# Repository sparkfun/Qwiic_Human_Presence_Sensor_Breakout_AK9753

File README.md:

SparkFun Qwiic Human Presence Sensor (AK9753)
========================================

[*SparkFun Qwiic Human Presence Sensor (SEN-14349)*](https://www.sparkfun.com/products/14349)

The AK9753 Human Presence Sensor is a 4 channel NDIR sensor meant to detect human movement.

Repository Contents
-------------------

* **/Hardware** - Eagle design files (.brd, .sch)
* **/Libraries** - Libraries for use with the SparkFun Human Presence Sensor Breakout - AK9753 (Qwiic).
* **/Production** - Production panel files (.brd)

Documentation
--------------
* **[Library](https://github.com/sparkfun/SparkFun_AK975x_Arduino_Library)** - Arduino library for the AK9753.
* **[Hookup Guide](https://learn.sparkfun.com/tutorials/qwiic-human-presence-sensor-ak9753-hookup-guide)** - Basic hookup guide for the Qwiic Human Presence Sensor.

Product Versions
----------------
* [SEN-14349](https://www.sparkfun.com/products/14349)- The AK9753 Human Presence Sensor is a 4 channel NDIR sensor meant to detect human movement.

License Information
-------------------

This product is _**open source**_! 

Please review the LICENSE.md file for license information. 

If you have any questions or concerns on licensing, please contact techsupport@sparkfun.com.

Distributed as-is; no warranty is given.

- Your friends at SparkFun.

_<COLLABORATION CREDIT>_

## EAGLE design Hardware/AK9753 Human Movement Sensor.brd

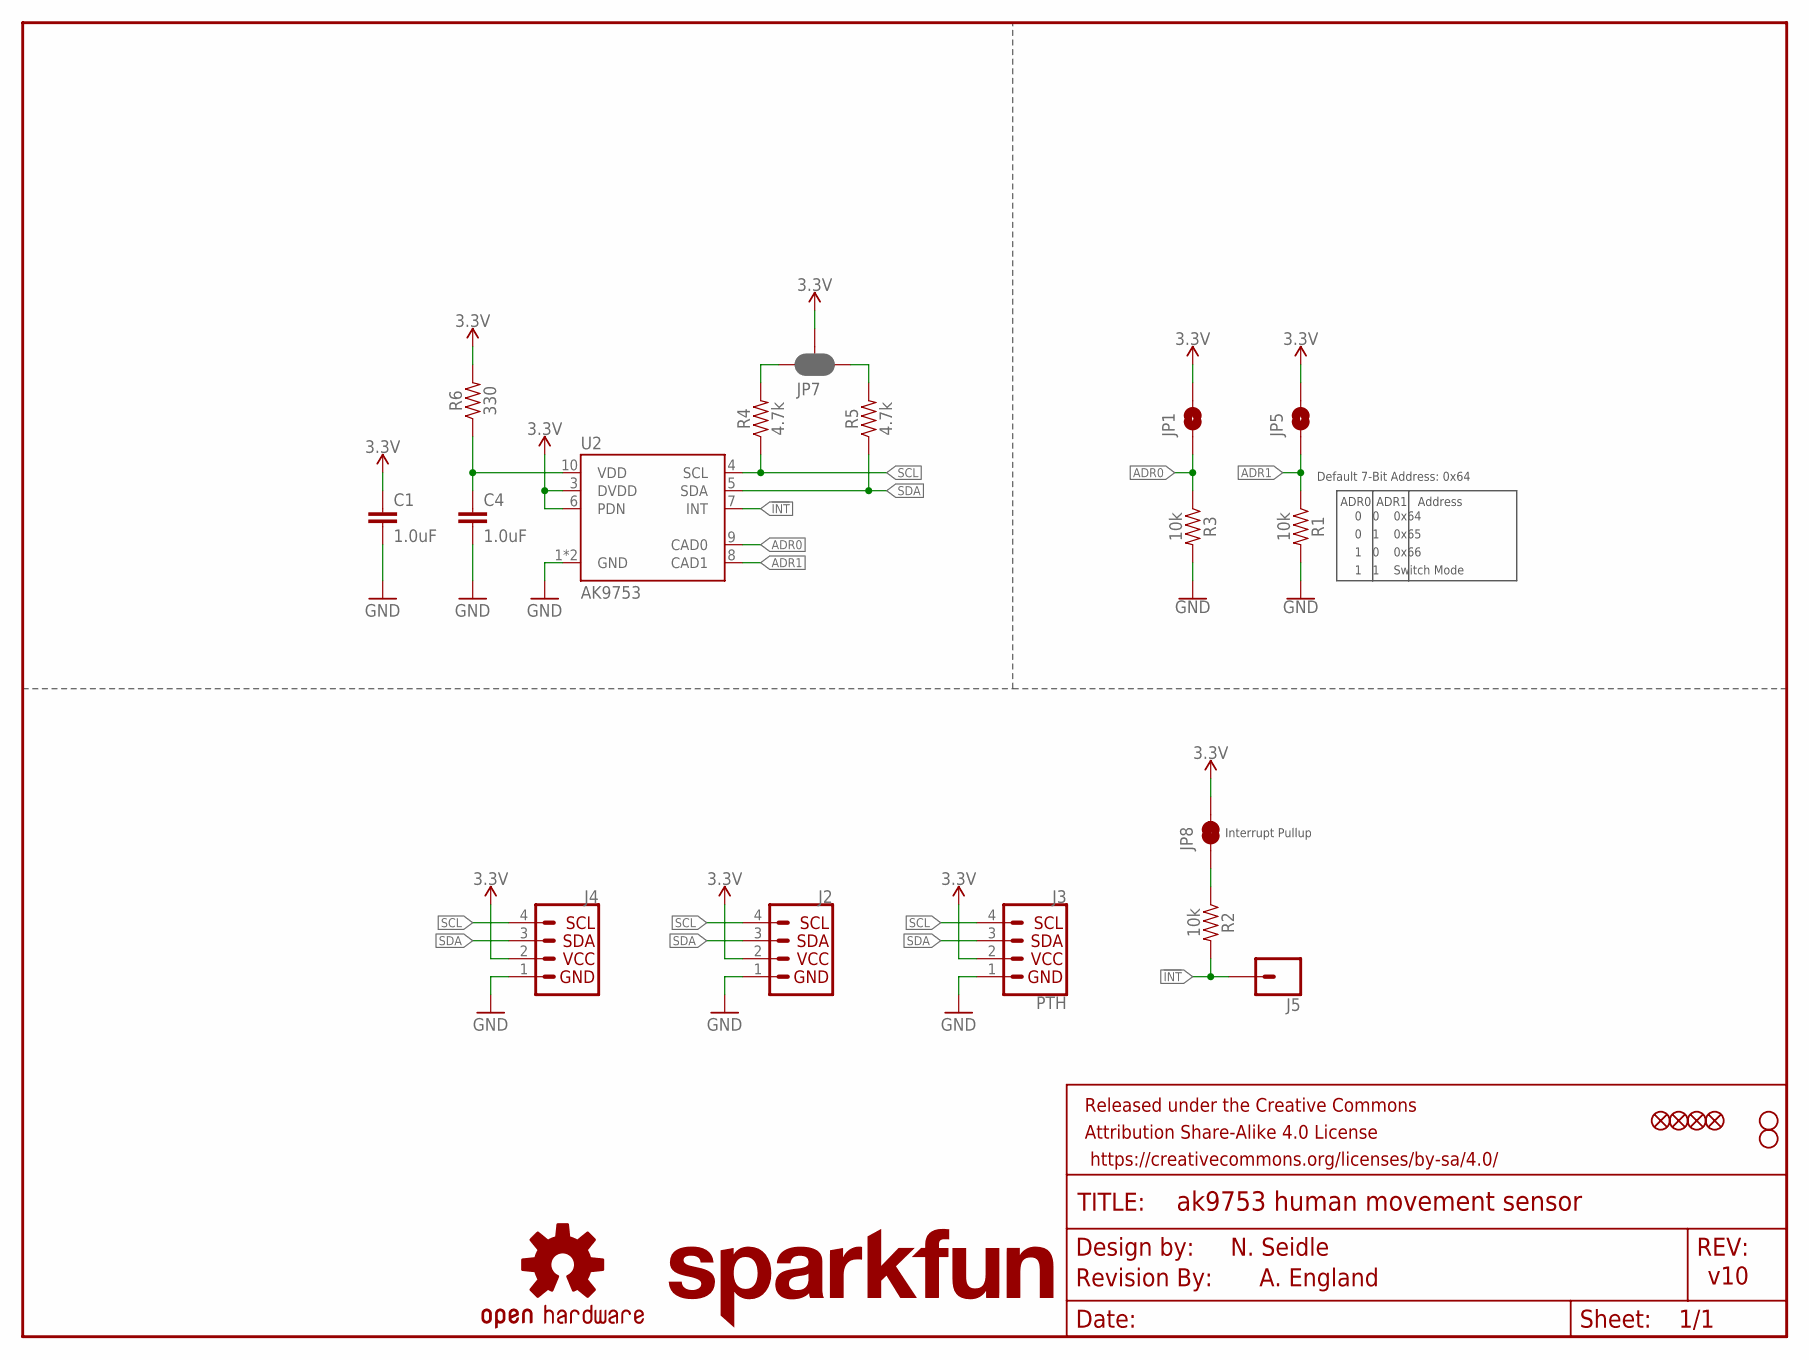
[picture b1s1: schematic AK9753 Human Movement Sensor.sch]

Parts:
C1, C4: 1.0uF; 0603
FRAME1: FRAME-LETTER; CREATIVE_COMMONS
J2, J4: QWIIC_CONNECTORJS-1MM; 1X04_1MM_RA
J3: PTH; 1X04_NO_SILK
J5: CONN_01PTH_NO_SILK_YES_STOP; 1X01_NO_SILK
JP1, JP5: JUMPER-SMT_2_NO_SILK; SMT-JUMPER_2_NO_SILK
JP2, JP6, JP9, JP10: FIDUCIALUFIDUCIAL; MICRO-FIDUCIAL
JP3, JP4: STAND-OFF
JP7: JUMPER-SMT_3_2-NC_PASTE_SILK; SMT-JUMPER_3_2-NC_PASTE_SILK
JP8: JUMPER-SMT_2_NC_TRACE_SILK; SMT-JUMPER_2_NC_TRACE_SILK
LOGO1: OSHW-LOGOMINI; OSHW-LOGO-MINI
LOGO2: SFE_LOGO_NAME.1_INCH; SFE_LOGO_NAME_.1
LOGO3: REVISION
R1, R2, R3: 10k; 0603
R4, R5: 4.7k; 0603
R6: 330; 0603
U2: AK9753; SON10

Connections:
3.3V: C1.1, J2.2, J3.2, J4.2, JP1.2, JP5.2, JP7.2, JP8.2, R6.2, U2.3 (DVDD), U2.6 (PDN)
!INT: J5.1, R2.2, U2.7 (INT)
ADR0: JP1.1, R3.1, U2.9 (CAD0)
ADR1: JP5.1, R1.1, U2.8 (CAD1)
GND: C1.2, C4.2, J2.1, J3.1, J4.1, R1.2, R3.2, U2.1 (GND), U2.2 (GND)
unnamed: JP7.1, R5.2
unnamed: JP7.3, R4.2
unnamed: JP8.1, R2.1
SCL: J2.4, J3.4, J4.4, R4.1, U2.4 (SCL)
SDA: J2.3, J3.3, J4.3, R5.1, U2.5 (SDA)
VDD: C4.1, R6.1, U2.10 (VDD)

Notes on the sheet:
N. Seidle
v10
Default 7-Bit Address: 0x64
ADR0
0 0 0x64
ADR1
Address
0 1 0x65
1 0 0x66
1 1 Switch Mode
A. England
Interrupt Pullup

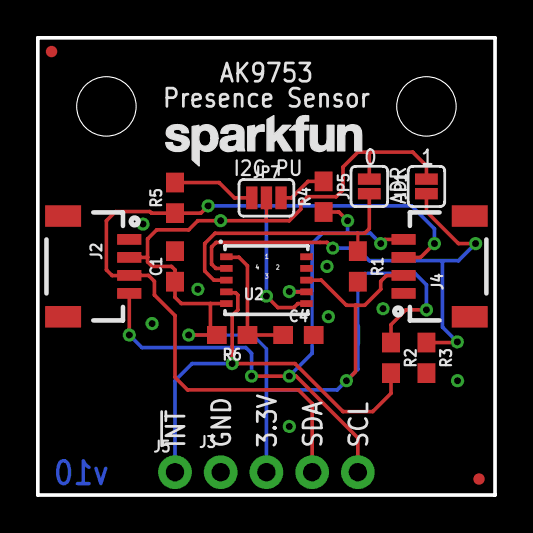
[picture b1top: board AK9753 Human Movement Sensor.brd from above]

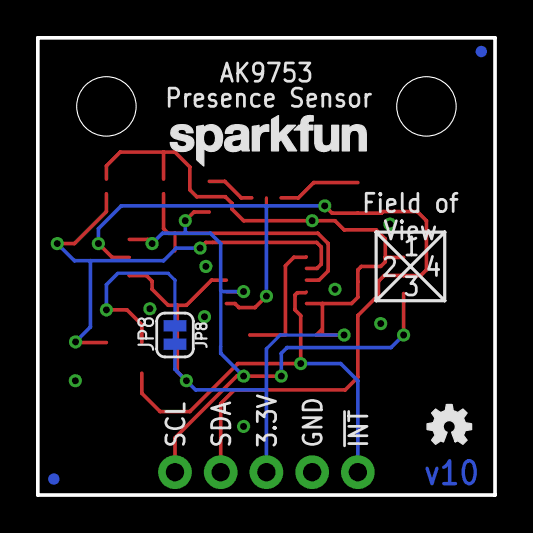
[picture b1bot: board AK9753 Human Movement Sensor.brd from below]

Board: 2 copper layers, 25.4 x 25.4 mm, 28 parts (5 on the bottom side), 11 nets.

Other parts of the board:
U$2: SFE_LOGO_NAME_.1

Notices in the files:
parts and their libraries:
SparkFun-Resistors: Licensing: Creative Commons ShareAlike 4.0 International - https://creativecommons.org/licenses/by-sa/4.0
SparkFun-Aesthetics: Released under the Creative Commons Attribution Share-Alike 4.0 License
SparkFun-Aesthetics: https://creativecommons.org/licenses/by-sa/4.0
